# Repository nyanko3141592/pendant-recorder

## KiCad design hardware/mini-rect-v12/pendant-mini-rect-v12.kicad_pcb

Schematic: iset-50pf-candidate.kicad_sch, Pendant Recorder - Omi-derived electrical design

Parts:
C1, C2, C3, C6, C9, C22, C26: 100n; C_0402_1005Metric
C4: 10u; C_0603_1608Metric
C5: 4.7u; C_0603_1608Metric
C7, C16, C25: 1u; C_0402_1005Metric
C11, C12: 10p tentative; C_0402_1005Metric
C13: 2.2u 10V; C_0402_1005Metric
C14: 2.2u; C_0402_1005Metric
C15: 10u 10V effective >=1u; C_0603_1608Metric
C27: 22u effective TBD; C_0603_1608Metric
C28: 10n; C_0402_1005Metric
C29: 100n 10V; C_0402_1005Metric
C30: 50p 50V C0G; C_0402_1005Metric
D6: amber LED 0402 TBD; LED_0402_1005Metric
J1: USB4105-GF-A (candidate); USB_C_GCT_USB4105_GroundLand112
J2: 0781710003 / 100mAh protected NTC pack TBD; Molex_Pico-EZmate_78171-0003_1x03-1MP_P1.20mm_Vertical
J3: TC2030 SWD target pads; Tag-Connect_TC2030-IDC-NL_2x03_P1.27mm_Vertical
Q3: 2N7002 (VBUS detect); SOT-23
Q4: 2N7002; SOT-23
R1: 0R; R_0402_1005Metric
R2: 10k; R_0402_1005Metric
R3, R4, R12, R13, R15, R22, R36: 100k; R_0402_1005Metric
R6, R7: 5.1k 1%; R_0402_1005Metric
R10: 15k 1%; R_0402_1005Metric
R11: 20k 1%; R_0402_1005Metric
R14: 1M; R_0402_1005Metric
R21, R23: 22R tentative; R_0402_1005Metric
R24, R25, R28: 47k; R_0402_1005Metric
R32: 6.8k tentative; R_0402_1005Metric
R33, R34: 1M 1%; R_0402_1005Metric
R35, R37, R38, R40, R43: 10k 1%; R_0402_1005Metric
R39: 12.1k 1%; R_0402_1005Metric
R41: 8.25k 1%; R_0402_1005Metric
R42: 24k 1%; R_0402_1005Metric
SW1: B3U-1000P (candidate); SW_SPST_B3U-1000P
TP1, TP2, TP3, TP5, TP6: TestPoint; TestPoint_Pad_D1.0mm
U1: STM32U535CEU6; QFN-48-1EP_7x7mm_P0.5mm_EP5.6x5.6mm
U2: USBLC6-2P6; SOT-666
U3: BQ25185DLHR; Texas_DLH0010A_WSON-10-1EP_2.2x2mm_P0.4mm_EP0.9x1.5mm
U4: TPS7A0233PDBVR; SOT-23-5
U8: IM69D130V01XTSA1; Infineon_PG-LLGA-5-1
U10: TPS22916CYFPR; TPS22916_YFP4
U11: CSNP16GCR01-AOW; CSNP16GCR01_AOW_LGA8
U12: TLV7042DDFR; SOT-23-8
Y1: 32.768kHz CL=7pF TBD; Crystal_SMD_2012-2Pin_2.0x1.2mm

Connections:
/BAT: C14.1, J2.1 (PACK+), R33.1, TP1.1, U3.2 (BAT)
/BAT_ADC: C28.1, R33.2, R34.1, U1.11 (PA1)
/BAT_TS: J2.2 (PACK_NTC), R37.2, U12.2 (INA-), U12.5 (INB+)
/BOOT0: R3.1, U1.44 (PH3)
/BUTTON_N: R4.2, SW1.1, U1.26 (PB13)
/CC1: J1.A5 (CC1), R6.1
/CC2: J1.B5 (CC2), R7.1
/CHARGER_TS: R35.1, U3.6 (TS_MR)
/CHG_ALLOW: R43.1, U1.20 (PB2)
/CHG_GUARD_GATE: Q4.1 (G), R36.1, R43.2, U12.1 (OUTA), U12.7 (OUTB)
/CHG_INHIBIT_GATE: Q4.3 (D), R12.2, U3.4 (CE_N)
/CHG_N: R11.2, U1.27 (PB14), U3.9 (STAT1)
/GND: C1.2, C2.2, C3.2, C4.2, C5.2, C6.2, C7.2, C9.2, C11.2, C12.2, C13.2, C14.2, C15.2, C16.2, C22.2, C25.2, C26.2, C27.2, C28.2, C29.2, C30.2, D6.1 (K), J1.A1 (GND), J1.A12 (GND), J1.B1 (GND), J1.B12 (GND), J1.SH (SHIELD), J2.3 (PACK-), J3.5 (GND), Q3.2 (S), Q4.2 (S), R3.2, R6.2, R7.2, R10.2, R14.2, R22.2, R34.2, R35.2, R36.2, R39.2, R41.2, R42.2, SW1.2, TP6.1, U1.8 (VSSA), U1.23 (VSS), U1.35 (VSS), U1.47 (VSS), U1.49 (VSS), U2.2 (GND), U3.5 (GND), U3.11 (EP), U4.2 (GND), U8.4 (SELECT), U8.5 (GND), U10.B1 (GND), U11.4 (VSS), U12.4 (VEE)
/ILIM_VSET: R42.1, U3.7 (ILIM_VSET)
/ISET: C30.1, R10.1, U3.8 (ISET)
/LSE_IN: C11.1, U1.3 (PC14), Y1.1
/LSE_OUT: C12.1, U1.4 (PC15), Y1.2
/NRST: C9.1, J3.3 (nRESET), R2.2, U1.7 (NRST)
/PDM_CLK: R21.2, U8.3 (CLOCK)
/PDM_CLK_MCU: R21.1, U1.39 (PB3)
/PDM_DATA: U1.40 (PB4), U8.1 (DATA)
/SD_CLK: R23.2, U11.3 (CLK)
/SD_CLK_MCU: R23.1, U1.15 (PA5)
/SD_CS_N: R28.2, U1.14 (PA4), U11.2 (CS_N)
/SD_EN: R22.1, U1.18 (PB0), U10.B2 (ON)
/SD_MISO: R25.2, U1.16 (PA6), U11.6 (DO)
/SD_MOSI: R24.2, U1.17 (PA7), U11.5 (DI)
/SD_V3: C26.1, C27.1, R24.1, R25.1, R28.1, TP5.1, U10.A1 (VOUT), U11.8 (VCC)
/STATUS_LED: R32.1, U1.29 (PA8)
/STATUS_LED_A: D6.2 (A), R32.2
/SWCLK: J3.4 (SWCLK), U1.37 (PA14)
/SWDIO: J3.2 (SWDIO), U1.34 (PA13)
/SYS: C15.1, TP2.1, U3.1 (SYS), U4.1 (IN), U4.3 (EN)
/TS_COLD_REF: R38.2, R39.1, U12.3 (INA+)
/TS_HOT_REF: R40.2, R41.1, U12.6 (INB-)
/USB_DM: J1.A7 (D-), J1.B7 (D-), U1.32 (PA11), U2.3 (IO2), U2.4 (IO2)
/USB_DP: J1.A6 (D+), J1.B6 (D+), U1.33 (PA12), U2.1 (IO1), U2.6 (IO1)
/V3V3: C1.1, C2.1, C3.1, C4.1, C16.1, C22.1, C25.1, J3.1 (VTref), R1.1, R2.1, R4.1, R11.1, R15.1, TP3.1, U1.1 (VBAT), U1.24 (VDD), U1.36 (VDD), U1.48 (VDD), U4.5 (OUT), U8.2 (VDD), U10.A2 (VIN)
/VBUS: C13.1, C29.1, J1.A4 (VBUS), J1.A9 (VBUS), J1.B4 (VBUS), J1.B9 (VBUS), R12.1, R13.1, R37.1, R38.1, R40.1, U2.5 (VBUS), U3.10 (IN), U12.8 (VCC)
/VBUS_GATE: Q3.1 (G), R13.2, R14.1
/VBUS_N: Q3.3 (D), R15.2, U1.10 (PA0)
/VCAP: C5.1, U1.22 (VCAP)
/VDDA: C6.1, C7.1, R1.2, U1.9 (VDDA)

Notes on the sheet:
01 MCU / RTC / UI
02 USB-C / CHARGER
03 POWER / FUEL GAUGE
04 AUDIO / SD / INDICATORS
ENGINEERING DRAFT - NOT FOR FABRICATION - See hardware/mini-rect-v12/README.md

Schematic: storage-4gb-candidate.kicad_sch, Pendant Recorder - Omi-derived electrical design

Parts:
C1, C2, C3, C6, C9, C22, C26: 100n; C_0402_1005Metric
C4: 10u; C_0603_1608Metric
C5: 4.7u; C_0603_1608Metric
C7, C16, C25: 1u; C_0402_1005Metric
C11, C12: 10p tentative; C_0402_1005Metric
C13: 2.2u 10V; C_0402_1005Metric
C14: 2.2u; C_0402_1005Metric
C15: 10u 10V effective >=1u; C_0603_1608Metric
C27: 22u effective TBD; C_0603_1608Metric
C28: 10n; C_0402_1005Metric
C29: 100n 10V; C_0402_1005Metric
C30: 50p 50V C0G; C_0402_1005Metric
D6: amber LED 0402 TBD; LED_0402_1005Metric
J1: USB4105-GF-A (candidate); USB_C_GCT_USB4105_GroundLand112
J2: 0781710003 / 100mAh protected NTC pack TBD; Molex_Pico-EZmate_78171-0003_1x03-1MP_P1.20mm_Vertical
J3: TC2030 SWD target pads; Tag-Connect_TC2030-IDC-NL_2x03_P1.27mm_Vertical
Q3: 2N7002 (VBUS detect); SOT-23
Q4: 2N7002; SOT-23
R1: 0R; R_0402_1005Metric
R2: 10k; R_0402_1005Metric
R3, R4, R12, R13, R15, R22, R36: 100k; R_0402_1005Metric
R6, R7: 5.1k 1%; R_0402_1005Metric
R10: 15k 1%; R_0402_1005Metric
R11: 20k 1%; R_0402_1005Metric
R14: 1M; R_0402_1005Metric
R21, R23: 22R tentative; R_0402_1005Metric
R24, R25, R28: 47k; R_0402_1005Metric
R32: 6.8k tentative; R_0402_1005Metric
R33, R34: 1M 1%; R_0402_1005Metric
R35, R37, R38, R40, R43: 10k 1%; R_0402_1005Metric
R39: 12.1k 1%; R_0402_1005Metric
R41: 8.25k 1%; R_0402_1005Metric
R42: 24k 1%; R_0402_1005Metric
SW1: B3U-1000P (candidate); SW_SPST_B3U-1000P
TP1, TP2, TP3, TP5, TP6: TestPoint; TestPoint_Pad_D1.0mm
U1: STM32U535CEU6; QFN-48-1EP_7x7mm_P0.5mm_EP5.6x5.6mm
U2: USBLC6-2P6; SOT-666
U3: BQ25185DLHR; Texas_DLH0010A_WSON-10-1EP_2.2x2mm_P0.4mm_EP0.9x1.5mm
U4: TPS7A0233PDBVR; SOT-23-5
U8: IM69D130V01XTSA1; Infineon_PG-LLGA-5-1
U10: TPS22916CYFPR; TPS22916_YFP4
U11: CSNP32GCR01-BOW; CSNP32GCR01_LGA8
U12: TLV7042DDFR; SOT-23-8
Y1: 32.768kHz CL=7pF TBD; Crystal_SMD_2012-2Pin_2.0x1.2mm

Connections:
/BAT: C14.1, J2.1 (PACK+), R33.1, TP1.1, U3.2 (BAT)
/BAT_ADC: C28.1, R33.2, R34.1, U1.11 (PA1)
/BAT_TS: J2.2 (PACK_NTC), R37.2, U12.2 (INA-), U12.5 (INB+)
/BOOT0: R3.1, U1.44 (PH3)
/BUTTON_N: R4.2, SW1.1, U1.26 (PB13)
/CC1: J1.A5 (CC1), R6.1
/CC2: J1.B5 (CC2), R7.1
/CHARGER_TS: R35.1, U3.6 (TS_MR)
/CHG_ALLOW: R43.1, U1.20 (PB2)
/CHG_GUARD_GATE: Q4.1 (G), R36.1, R43.2, U12.1 (OUTA), U12.7 (OUTB)
/CHG_INHIBIT_GATE: Q4.3 (D), R12.2, U3.4 (CE_N)
/CHG_N: R11.2, U1.27 (PB14), U3.9 (STAT1)
/GND: C1.2, C2.2, C3.2, C4.2, C5.2, C6.2, C7.2, C9.2, C11.2, C12.2, C13.2, C14.2, C15.2, C16.2, C22.2, C25.2, C26.2, C27.2, C28.2, C29.2, C30.2, D6.1 (K), J1.A1 (GND), J1.A12 (GND), J1.B1 (GND), J1.B12 (GND), J1.SH (SHIELD), J2.3 (PACK-), J3.5 (GND), Q3.2 (S), Q4.2 (S), R3.2, R6.2, R7.2, R10.2, R14.2, R22.2, R34.2, R35.2, R36.2, R39.2, R41.2, R42.2, SW1.2, TP6.1, U1.8 (VSSA), U1.23 (VSS), U1.35 (VSS), U1.47 (VSS), U1.49 (VSS), U2.2 (GND), U3.5 (GND), U3.11 (EP), U4.2 (GND), U8.4 (SELECT), U8.5 (GND), U10.B1 (GND), U11.4 (VSS), U12.4 (VEE)
/ILIM_VSET: R42.1, U3.7 (ILIM_VSET)
/ISET: C30.1, R10.1, U3.8 (ISET)
/LSE_IN: C11.1, U1.3 (PC14), Y1.1
/LSE_OUT: C12.1, U1.4 (PC15), Y1.2
/NRST: C9.1, J3.3 (nRESET), R2.2, U1.7 (NRST)
/PDM_CLK: R21.2, U8.3 (CLOCK)
/PDM_CLK_MCU: R21.1, U1.39 (PB3)
/PDM_DATA: U1.40 (PB4), U8.1 (DATA)
/SD_CLK: R23.2, U11.3 (CLK)
/SD_CLK_MCU: R23.1, U1.15 (PA5)
/SD_CS_N: R28.2, U1.14 (PA4), U11.2 (CS_N)
/SD_EN: R22.1, U1.18 (PB0), U10.B2 (ON)
/SD_MISO: R25.2, U1.16 (PA6), U11.6 (DO)
/SD_MOSI: R24.2, U1.17 (PA7), U11.5 (DI)
/SD_V3: C26.1, C27.1, R24.1, R25.1, R28.1, TP5.1, U10.A1 (VOUT), U11.8 (VCC)
/STATUS_LED: R32.1, U1.29 (PA8)
/STATUS_LED_A: D6.2 (A), R32.2
/SWCLK: J3.4 (SWCLK), U1.37 (PA14)
/SWDIO: J3.2 (SWDIO), U1.34 (PA13)
/SYS: C15.1, TP2.1, U3.1 (SYS), U4.1 (IN), U4.3 (EN)
/TS_COLD_REF: R38.2, R39.1, U12.3 (INA+)
/TS_HOT_REF: R40.2, R41.1, U12.6 (INB-)
/USB_DM: J1.A7 (D-), J1.B7 (D-), U1.32 (PA11), U2.3 (IO2), U2.4 (IO2)
/USB_DP: J1.A6 (D+), J1.B6 (D+), U1.33 (PA12), U2.1 (IO1), U2.6 (IO1)
/V3V3: C1.1, C2.1, C3.1, C4.1, C16.1, C22.1, C25.1, J3.1 (VTref), R1.1, R2.1, R4.1, R11.1, R15.1, TP3.1, U1.1 (VBAT), U1.24 (VDD), U1.36 (VDD), U1.48 (VDD), U4.5 (OUT), U8.2 (VDD), U10.A2 (VIN)
/VBUS: C13.1, C29.1, J1.A4 (VBUS), J1.A9 (VBUS), J1.B4 (VBUS), J1.B9 (VBUS), R12.1, R13.1, R37.1, R38.1, R40.1, U2.5 (VBUS), U3.10 (IN), U12.8 (VCC)
/VBUS_GATE: Q3.1 (G), R13.2, R14.1
/VBUS_N: Q3.3 (D), R15.2, U1.10 (PA0)
/VCAP: C5.1, U1.22 (VCAP)
/VDDA: C6.1, C7.1, R1.2, U1.9 (VDDA)

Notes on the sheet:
01 MCU / RTC / UI
02 USB-C / CHARGER
03 POWER / FUEL GAUGE
04 AUDIO / SD / INDICATORS
ENGINEERING DRAFT - NOT FOR FABRICATION - See hardware/mini-rect-v12/README.md

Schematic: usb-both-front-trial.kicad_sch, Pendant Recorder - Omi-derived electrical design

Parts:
C1, C2, C3, C6, C9, C22, C26: 100n; C_0402_1005Metric
C4: 10u; C_0603_1608Metric
C5: 4.7u; C_0603_1608Metric
C7, C16, C25: 1u; C_0402_1005Metric
C11, C12: 10p tentative; C_0402_1005Metric
C13: 2.2u 10V; C_0402_1005Metric
C14: 2.2u; C_0402_1005Metric
C15: 10u 10V effective >=1u; C_0603_1608Metric
C27: 22u effective TBD; C_0603_1608Metric
C28: 10n; C_0402_1005Metric
C29: 100n 10V; C_0402_1005Metric
C30: 10n tentative; C_0402_1005Metric
D6: amber LED 0402 TBD; LED_0402_1005Metric
J1: USB4105-GF-A (candidate); USB_C_GCT_USB4105_GroundLand112
J2: 0781710003 / 100mAh protected NTC pack TBD; Molex_Pico-EZmate_78171-0003_1x03-1MP_P1.20mm_Vertical
J3: TC2030 SWD target pads; Tag-Connect_TC2030-IDC-NL_2x03_P1.27mm_Vertical
Q3: 2N7002 (VBUS detect); SOT-23
Q4: 2N7002; SOT-23
R1: 0R; R_0402_1005Metric
R2: 10k; R_0402_1005Metric
R3, R4, R12, R13, R15, R22, R36: 100k; R_0402_1005Metric
R6, R7: 5.1k 1%; R_0402_1005Metric
R10: 15k 1%; R_0402_1005Metric
R11: 20k 1%; R_0402_1005Metric
R14: 1M; R_0402_1005Metric
R21, R23: 22R tentative; R_0402_1005Metric
R24, R25, R28: 47k; R_0402_1005Metric
R32: 6.8k tentative; R_0402_1005Metric
R33, R34: 1M 1%; R_0402_1005Metric
R35, R37, R38, R40, R43: 10k 1%; R_0402_1005Metric
R39: 12.1k 1%; R_0402_1005Metric
R41: 8.25k 1%; R_0402_1005Metric
R42: 24k 1%; R_0402_1005Metric
SW1: B3U-1000P (candidate); SW_SPST_B3U-1000P
TP1, TP2, TP3, TP5, TP6: TestPoint; TestPoint_Pad_D1.0mm
U1: STM32U535CEU6; QFN-48-1EP_7x7mm_P0.5mm_EP5.6x5.6mm
U2: USBLC6-2P6; SOT-666
U3: BQ25185DLHR; Texas_DLH0010A_WSON-10-1EP_2.2x2mm_P0.4mm_EP0.9x1.5mm
U4: TPS7A0233PDBVR; SOT-23-5
U8: IM69D130V01XTSA1; Infineon_PG-LLGA-5-1
U10: TPS22916CYFPR; TPS22916_YFP4
U11: CSNP16GCR01-AOW; CSNP16GCR01_AOW_LGA8
U12: TLV7042DDFR; SOT-23-8
Y1: 32.768kHz CL=7pF TBD; Crystal_SMD_2012-2Pin_2.0x1.2mm

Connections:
/BAT: C14.1, J2.1 (PACK+), R33.1, TP1.1, U3.2 (BAT)
/BAT_ADC: C28.1, R33.2, R34.1, U1.11 (PA1)
/BAT_TS: J2.2 (PACK_NTC), R37.2, U12.2 (INA-), U12.5 (INB+)
/BOOT0: R3.1, U1.44 (PH3)
/BUTTON_N: R4.2, SW1.1, U1.26 (PB13)
/CC1: J1.A5 (CC1), R6.1
/CC2: J1.B5 (CC2), R7.1
/CHARGER_TS: R35.1, U3.6 (TS_MR)
/CHG_ALLOW: R43.1, U1.20 (PB2)
/CHG_GUARD_GATE: Q4.1 (G), R36.1, R43.2, U12.1 (OUTA), U12.7 (OUTB)
/CHG_INHIBIT_GATE: Q4.3 (D), R12.2, U3.4 (CE_N)
/CHG_N: R11.2, U1.27 (PB14), U3.9 (STAT1)
/GND: C1.2, C2.2, C3.2, C4.2, C5.2, C6.2, C7.2, C9.2, C11.2, C12.2, C13.2, C14.2, C15.2, C16.2, C22.2, C25.2, C26.2, C27.2, C28.2, C29.2, C30.2, D6.1 (K), J1.A1 (GND), J1.A12 (GND), J1.B1 (GND), J1.B12 (GND), J1.SH (SHIELD), J2.3 (PACK-), J3.5 (GND), Q3.2 (S), Q4.2 (S), R3.2, R6.2, R7.2, R10.2, R14.2, R22.2, R34.2, R35.2, R36.2, R39.2, R41.2, R42.2, SW1.2, TP6.1, U1.8 (VSSA), U1.23 (VSS), U1.35 (VSS), U1.47 (VSS), U1.49 (VSS), U2.2 (GND), U3.5 (GND), U3.11 (EP), U4.2 (GND), U8.4 (SELECT), U8.5 (GND), U10.B1 (GND), U11.4 (VSS), U12.4 (VEE)
/ILIM_VSET: R42.1, U3.7 (ILIM_VSET)
/ISET: C30.1, R10.1, U3.8 (ISET)
/LSE_IN: C11.1, U1.3 (PC14), Y1.1
/LSE_OUT: C12.1, U1.4 (PC15), Y1.2
/NRST: C9.1, J3.3 (nRESET), R2.2, U1.7 (NRST)
/PDM_CLK: R21.2, U8.3 (CLOCK)
/PDM_CLK_MCU: R21.1, U1.39 (PB3)
/PDM_DATA: U1.40 (PB4), U8.1 (DATA)
/SD_CLK: R23.2, U11.3 (CLK)
/SD_CLK_MCU: R23.1, U1.15 (PA5)
/SD_CS_N: R28.2, U1.14 (PA4), U11.2 (CS_N)
/SD_EN: R22.1, U1.18 (PB0), U10.B2 (ON)
/SD_MISO: R25.2, U1.16 (PA6), U11.6 (DO)
/SD_MOSI: R24.2, U1.17 (PA7), U11.5 (DI)
/SD_V3: C26.1, C27.1, R24.1, R25.1, R28.1, TP5.1, U10.A1 (VOUT), U11.8 (VCC)
/STATUS_LED: R32.1, U1.29 (PA8)
/STATUS_LED_A: D6.2 (A), R32.2
/SWCLK: J3.4 (SWCLK), U1.37 (PA14)
/SWDIO: J3.2 (SWDIO), U1.34 (PA13)
/SYS: C15.1, TP2.1, U3.1 (SYS), U4.1 (IN), U4.3 (EN)
/TS_COLD_REF: R38.2, R39.1, U12.3 (INA+)
/TS_HOT_REF: R40.2, R41.1, U12.6 (INB-)
/USB_DM: J1.A7 (D-), J1.B7 (D-), U1.32 (PA11), U2.3 (IO2), U2.4 (IO2)
/USB_DP: J1.A6 (D+), J1.B6 (D+), U1.33 (PA12), U2.1 (IO1), U2.6 (IO1)
/V3V3: C1.1, C2.1, C3.1, C4.1, C16.1, C22.1, C25.1, J3.1 (VTref), R1.1, R2.1, R4.1, R11.1, R15.1, TP3.1, U1.1 (VBAT), U1.24 (VDD), U1.36 (VDD), U1.48 (VDD), U4.5 (OUT), U8.2 (VDD), U10.A2 (VIN)
/VBUS: C13.1, C29.1, J1.A4 (VBUS), J1.A9 (VBUS), J1.B4 (VBUS), J1.B9 (VBUS), R12.1, R13.1, R37.1, R38.1, R40.1, U2.5 (VBUS), U3.10 (IN), U12.8 (VCC)
/VBUS_GATE: Q3.1 (G), R13.2, R14.1
/VBUS_N: Q3.3 (D), R15.2, U1.10 (PA0)
/VCAP: C5.1, U1.22 (VCAP)
/VDDA: C6.1, C7.1, R1.2, U1.9 (VDDA)

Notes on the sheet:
01 MCU / RTC / UI
02 USB-C / CHARGER
03 POWER / FUEL GAUGE
04 AUDIO / SD / INDICATORS
ENGINEERING DRAFT - NOT FOR FABRICATION - See hardware/mini-rect-v12/README.md

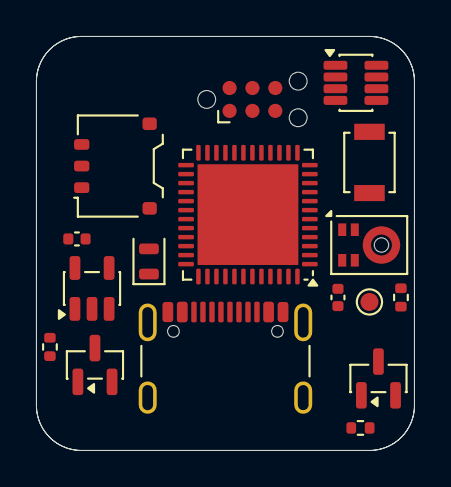
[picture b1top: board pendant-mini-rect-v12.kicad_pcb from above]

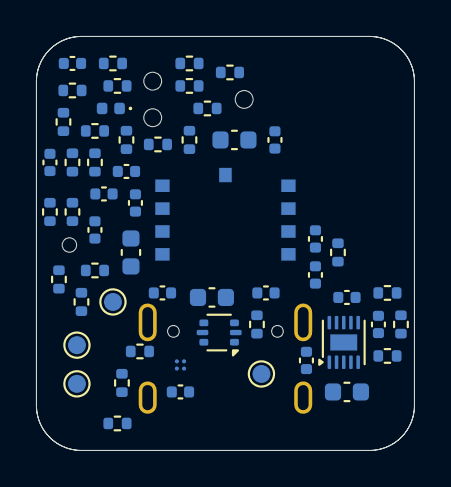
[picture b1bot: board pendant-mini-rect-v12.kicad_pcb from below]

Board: 6 copper layers, 21.0 x 23.0 mm, 72 parts (55 on the bottom side), 43 nets, no tracks yet.

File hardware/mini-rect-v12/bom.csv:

Reference,Part/value,Footprint,Design note
U1,STM32U535CEU6,Package_DFN_QFN:QFN-48-1EP_7x7mm_P0.5mm_EP5.6x5.6mm,512KB Flash/274KB RAM; non-SMPS UFQFPN48. PB3/PB4 ADF AF3; PA5/6/7 SPI1 AF5. VDD USB shared 3.3V. JLC acceptance and pin review pending.
C1,100n,Capacitor_SMD:C_0402_1005Metric,
C4,10u,Capacitor_SMD:C_0603_1608Metric,Main bulk capacitor; check startup and effective capacitance.
C9,100n,Capacitor_SMD:C_0402_1005Metric,
R2,10k,Resistor_SMD:R_0402_1005Metric,
Y1,32.768kHz CL=7pF TBD,Crystal:Crystal_SMD_2012-2Pin_2.0x1.2mm,
C11,10p tentative,Capacitor_SMD:C_0402_1005Metric,
C12,10p tentative,Capacitor_SMD:C_0402_1005Metric,
J3,TC2030 SWD target pads,Connector:Tag-Connect_TC2030-IDC-NL_2x03_P1.27mm_Vertical,TC2030-NL/CTX standard; completed STM32-compatible probe/cable; access with battery disconnected.
SW1,B3U-1000P (candidate),Button_Switch_SMD:SW_SPST_B3U-1000P,
R4,100k,Resistor_SMD:R_0402_1005Metric,
J1,USB4105-GF-A (candidate),PendantD1:USB_C_GCT_USB4105_GroundLand112,Exact footprint and shield pad numbering pending connector selection
R6,5.1k 1%,Resistor_SMD:R_0402_1005Metric,
R7,5.1k 1%,Resistor_SMD:R_0402_1005Metric,
U2,USBLC6-2P6,Package_TO_SOT_SMD:SOT-666,"ST DS4260 same 6-pin function diagram; smaller package, LCSC C15999 catalog; orientation/land pattern final audit pending."
C13,2.2u 10V,Capacitor_SMD:C_0402_1005Metric,
U3,BQ25185DLHR,Package_DFN_QFN:Texas_DLH0010A_WSON-10-1EP_2.2x2mm_P0.4mm_EP0.9x1.5mm,Integrated power path; 4.2V/100mA input via24k; 20mA charge via15k. Independent U12/Q4 battery NTC guard retained; internal TS biased10k is NOT battery temperature sensing.
R10,15k 1%,Resistor_SMD:R_0402_1005Metric,Approx22mA nominal versus listed100mAh pack max50mA; voltage/termination acceptance and actual pack datasheet remain unresolved.
R11,20k 1%,Resistor_SMD:R_0402_1005Metric,
C14,2.2u,Capacitor_SMD:C_0402_1005Metric,
J2,0781710003 / 100mAh protected NTC pack TBD,Connector_Molex:Molex_Pico-EZmate_78171-0003_1x03-1MP_P1.20mm_Vertical,15x17x6 pack envelope retained; vendor NTC/finished connector and harness unqualified.
R12,100k,Resistor_SMD:R_0402_1005Metric,100k VBUS pull-up defaults Q2 to charge inhibited; no MCU GPIO connection to5V.
C15,10u 10V effective >=1u,Capacitor_SMD:C_0603_1608Metric,SYS cap per TI; DC-bias capacitance must be qualified.
U4,TPS7A0233PDBVR,Package_TO_SOT_SMD:SOT-23-5,3.3V main rail: 48-pin MCU has no separate USB supply; dropout/capacity measurement required.
C16,1u,Capacitor_SMD:C_0402_1005Metric,
U8,IM69D130V01XTSA1,Sensor_Audio:Infineon_PG-LLGA-5-1,"Direct 3.3V PDM, bottom port; no AAD. 0.768MHz/decimation48 candidate for 16kHz; acoustic validation required."
R21,22R tentative,Resistor_SMD:R_0402_1005Metric,
C22,100n,Capacitor_SMD:C_0402_1005Metric,
U10,TPS22916CYFPR,Pendant:TPS22916_YFP4,Omi SD switch; power-off sequence must tristate ALL SD signals
R22,100k,Resistor_SMD:R_0402_1005Metric,
C25,1u,Capacitor_SMD:C_0402_1005Metric,
U11,CSNP16GCR01-AOW,Pendant:CSNP16GCR01_AOW_LGA8,"2GB class SPI SD NAND; C7527488. Datasheet pinout and max height0.90mm checked. Actual CSD capacity and busy current require qualification. 36h storage allocation budget1,131,544,576bytes including16MiB reserve."
R23,22R tentative,Resistor_SMD:R_0402_1005Metric,
R24,47k,Resistor_SMD:R_0402_1005Metric,
R25,47k,Resistor_SMD:R_0402_1005Metric,
R28,47k,Resistor_SMD:R_0402_1005Metric,
C26,100n,Capacitor_SMD:C_0402_1005Metric,
C27,22u effective TBD,Capacitor_SMD:C_0603_1608Metric,
TP1,TestPoint,TestPoint:TestPoint_Pad_D1.0mm,
TP2,TestPoint,TestPoint:TestPoint_Pad_D1.0mm,
TP3,TestPoint,TestPoint:TestPoint_Pad_D1.0mm,
TP5,TestPoint,TestPoint:TestPoint_Pad_D1.0mm,
TP6,TestPoint,TestPoint:TestPoint_Pad_D1.0mm,
R32,6.8k tentative,Resistor_SMD:R_0402_1005Metric,"LED current target 0.1-0.2mA; verify LED Vf, daylight readability and GPIO limits"
D6,amber LED 0402 TBD,LED_SMD:LED_0402_1005Metric,"Single status/battery indicator; firmware blinks on demand, normally dark."
C2,100n,Capacitor_SMD:C_0402_1005Metric,
C3,100n,Capacitor_SMD:C_0402_1005Metric,
C5,4.7u,Capacitor_SMD:C_0603_1608Metric,
C6,100n,Capacitor_SMD:C_0402_1005Metric,
C7,1u,Capacitor_SMD:C_0402_1005Metric,
R1,0R,Resistor_SMD:R_0402_1005Metric,
R3,100k,Resistor_SMD:R_0402_1005Metric,
Q3,2N7002 (VBUS detect),Package_TO_SOT_SMD:SOT-23,
R13,100k,Resistor_SMD:R_0402_1005Metric,
R14,1M,Resistor_SMD:R_0402_1005Metric,
R15,100k,Resistor_SMD:R_0402_1005Metric,
R33,1M 1%,Resistor_SMD:R_0402_1005Metric,"Battery divider 1:2; sample after settling, calibrate with VREFINT; not coulomb counting."
R34,1M 1%,Resistor_SMD:R_0402_1005Metric,"Battery divider 1:2; sample after settling, calibrate with VREFINT; not coulomb counting."
C28,10n,Capacitor_SMD:C_0402_1005Metric,"Battery divider 1:2; sample after settling, calibrate with VREFINT; not coulomb counting."
R35,10k 1%,Resistor_SMD:R_0402_1005Metric,Holds normal TS level when released; no floating TS/TTDM in intended circuit.
R36,100k,Resistor_SMD:R_0402_1005Metric,MCU reset/high-Z defaults to no charging permission.
R37,10k 1%,Resistor_SMD:R_0402_1005Metric,Ratiometric NTC excitation only while USB present; self-heating must be verified.
R38,10k 1%,Resistor_SMD:R_0402_1005Metric,
R39,12.1k 1%,Resistor_SMD:R_0402_1005Metric,Provisional external temperature window; requires actual supplied NTC R-T and tolerance. Do not authorize charging from this design alone.
R40,10k 1%,Resistor_SMD:R_0402_1005Metric,
R41,8.25k 1%,Resistor_SMD:R_0402_1005Metric,Provisional external temperature window; requires actual supplied NTC R-T and tolerance. Do not authorize charging from this design alone.
U12,TLV7042DDFR,Package_TO_SOT_SMD:SOT-23-8,Open-drain outputs wired together. Either temperature fault pulls Q4 gate low; no firmware override. 10k/B3370 pack assumption remains unqualified.
Q4,2N7002,Package_TO_SOT_SMD:SOT-23,Series pull-down permission chain. All three must conduct to release Q2. Body diodes oppose pull-down when off. Verify stack/leakage/transients.
C29,100n 10V,Capacitor_SMD:C_0402_1005Metric,Place adjacent to U12 supply pins.
R42,24k 1%,Resistor_SMD:R_0402_1005Metric,BQ25185 reference application; verify tolerance and low-current startup RC.
C30,10n tentative,Capacitor_SMD:C_0402_1005Metric,BQ25185 reference application; verify tolerance and low-current startup RC.
R43,10k 1%,Resistor_SMD:R_0402_1005Metric,MCU permission series resistor; limits current into comparator fault clamp.
